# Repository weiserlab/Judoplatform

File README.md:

A Platform for learning and prototyping low-power wireless embedded systems

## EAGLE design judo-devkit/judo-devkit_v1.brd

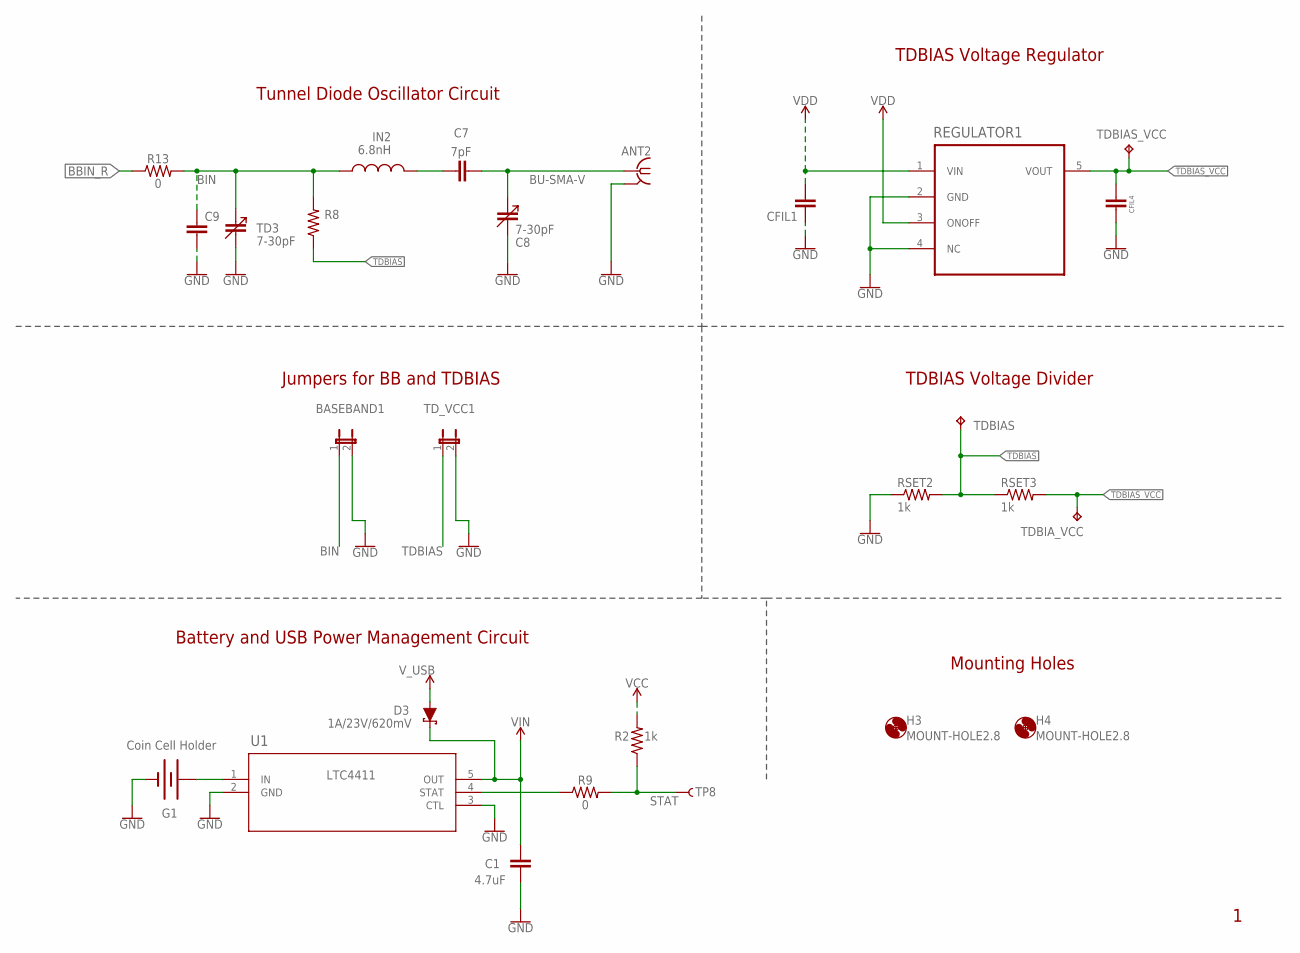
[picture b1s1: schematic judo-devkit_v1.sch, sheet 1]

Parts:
BASEBAND1: JP1E; JP1
C1: 4.7uF; C0603
C7: 7pF; C0603
C8: 7-30pF; CTZ3
C9: CAP-0603; 0603
CFIL1, CFIL4: 0805_1; 0805_1PRIMARY
D3: 1A/23V/620mV; SOD-323
G1: Coin Cell Holder; BATTCON_20MM_4LEGS
H3, H4: MOUNT-HOLE2.8; 2,8
IN2: 6.8nH; 0603_1PRIMARY
R2: 1k; 0603
R8: RESISTOR0805-RES; 0805
R9, R13: 0; 0603
REGULATOR1: S-1313B20; SOT23-5
RSET2, RSET3: 1k; R0603
TD3: 7-30pF; CTZ3
TDBIAS: TPPAD1-17; P1-17
TDBIAS_VCC: TPPAD1-17; P1-17
TDBIA_VCC: TPPAD1-17; P1-17
TD_VCC1: JP1E; JP1
TP8: TEST-POINT3X5; PAD.03X.05
TUNNELDIODE2: BU-SMA-V
U1: LTC4411ES5TRMPBF; SOT-5_S_LIT; MANUFACTURER_PART_NUMBER LTC4411

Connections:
ANT2: C7.2, C8.+ (3), TUNNELDIODE2.1
BBIN_R: R13.1; also elsewhere on the board
BIN: BASEBAND1.1, C9.1, IN2.1, R8.2, R13.2, TD3.+ (3)
GND: BASEBAND1.2, C1.1, C8.- (4), C9.2, CFIL1.1, CFIL4.2, G1.NEGATIVE (-), REGULATOR1.2 (GND), REGULATOR1.4 (NC), RSET2.1, TD3.- (4), TD_VCC1.2, TUNNELDIODE2.2, TUNNELDIODE2.3 (2), TUNNELDIODE2.4 (2), TUNNELDIODE2.5 (2), U1.2 (GND), U1.3 (CTL); also elsewhere on the board
unnamed: G1.POSITIVE@1 (+), G1.POSITIVE@2 (+), G1.POSITIVE@3 (+), G1.POSITIVE@4 (+), U1.1 (IN)
unnamed: R9.1, U1.4 (STAT)
unnamed: C7.1, IN2.2
STAT: R2.1, R9.2, TP8.1
TDBIAS: R8.1, RSET2.2, RSET3.1, TDBIAS.TP, TD_VCC1.1
TDBIAS_VCC: CFIL4.1, REGULATOR1.5 (VOUT), RSET3.2, TDBIAS_VCC.TP, TDBIA_VCC.TP
VCC: R2.2; also elsewhere on the board
VDD: CFIL1.2, REGULATOR1.1 (VIN), REGULATOR1.3 (ONOFF); also elsewhere on the board
VIN: C1.2, D3.C, U1.5 (OUT); also elsewhere on the board
V_USB: D3.A; also elsewhere on the board

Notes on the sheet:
Battery and USB Power Management Circuit
Tunnel Diode Oscillator Circuit
Jumpers for BB and TDBIAS
TDBIAS Voltage Divider
TDBIAS Voltage Regulator
Mounting Holes

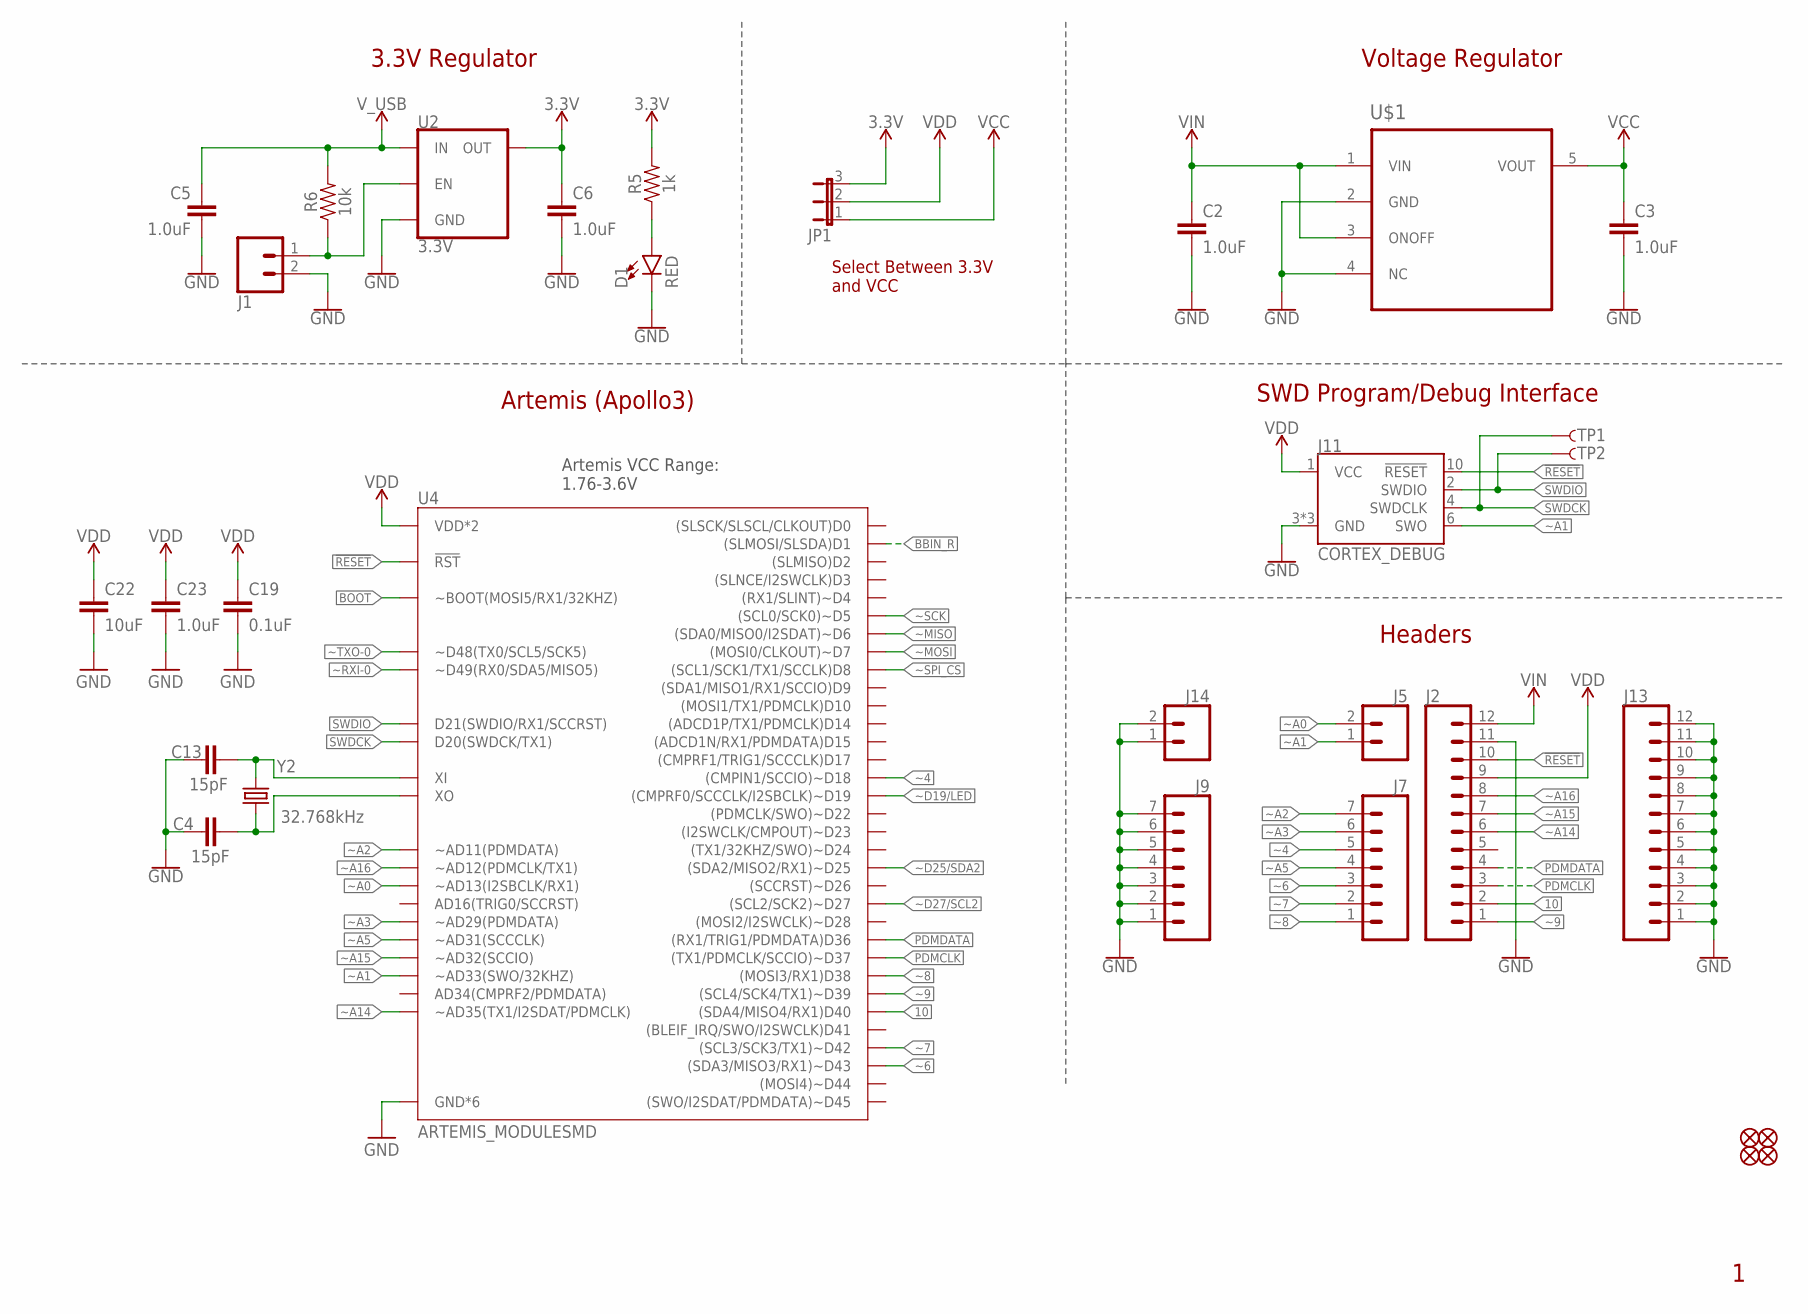
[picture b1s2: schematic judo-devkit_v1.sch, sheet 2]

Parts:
C2, C3, C5, C6, C23: 1.0uF; 0402-TIGHT
C4, C13: 15pF; 0603
C19: 0.1uF; 0402-TIGHT
C22: 10uF; 0603
D1: RED; LED-0603
FD1, FD2, FD3, FD4: FIDUCIALUFIDUCIAL; FIDUCIAL-MICRO
J1, J5, J14: CONN_021X02_NO_SILK; 1X02_NO_SILK
J2, J13: CONN_12NO_SILK; 1X12_NO_SILK
J7, J9: CONN_07NO_SILK; 1X07_NO_SILK
J11: CORTEX_DEBUG; 2X5-PTH-1.27MM-NO_SILK
JP1: JP2E; JP2
R5: 1k; 0603
R6: 10k; 0603
TP1, TP2: TEST-POINT3X5; PAD.03X.05
U2: 3.3V; SOT23-5
U4: ARTEMIS_MODULESMD; ARTEMIS_FP
U$1: CUSTOMCOMPONENTS_S-1313B20; CUSTOMCOMPONENTS_SOT23-5
Y2: 32.768kHz; CRYSTAL-SMD-3.2X1.5MM

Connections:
3.3V: C6.1, JP1.3, R5.2, U2.5 (OUT); also elsewhere on the board
10: J2.2, U4.D40 ((SDA4/MISO4/RX1)D40)
!RESET: J2.10, J11.10 (!RESET), U4.~RST (!RST); also elsewhere on the board
BBIN_R: U4.D1 ((SLMOSI/SLSDA)D1); also elsewhere on the board
BOOT: U4.BOOT (~BOOT(MOSI5/RX1/32KHZ)); also elsewhere on the board
GND: C2.2, C3.2, C4.1, C5.2, C6.2, C13.1, C19.1, C22.2, C23.2, D1.C, J1.2, J2.11, J9.1, J9.2, J9.3, J9.4, J9.5, J9.6, J9.7, J11.3 (GND), J11.5 (GND), J11.9 (GND), J13.1, J13.2, J13.3, J13.4, J13.5, J13.6, J13.7, J13.8, J13.9, J13.10, J13.11, J13.12, J14.1, J14.2, U2.2 (GND), U4.GND@1 (GND*6), U4.GND@22 (GND*6), U4.GND@38 (GND*6), U4.GND@39 (GND*6), U4.GND@47 (GND*6), U4.GND@59 (GND*6), U$1.2 (GND), U$1.4 (NC); also elsewhere on the board
unnamed: D1.A, R5.1
unnamed: C4.2, U4.XO, Y2.P$2 (2)
unnamed: C13.2, U4.XI, Y2.P$1 (1)
PDMCLK: J2.3, U4.~D37 ((TX1/PDMCLK/SCCIO)~D37)
PDMDATA: J2.4, U4.D36 ((RX1/TRIG1/PDMDATA)D36)
SWDCK: J11.4 (SWDCLK), TP1.1, U4.SWDCK (D20(SWDCK/TX1))
SWDIO: J11.2 (SWDIO), TP2.1, U4.SWDIO (D21(SWDIO/RX1/SCCRST))
VCC: C3.1, JP1.1, U$1.5 (VOUT); also elsewhere on the board
VDD: C19.2, C22.1, C23.1, J2.9, J11.1 (VCC), JP1.2, U4.VDD@36 (VDD*2), U4.VDD@37 (VDD*2); also elsewhere on the board
VIN: C2.1, J2.12, U$1.1 (VIN), U$1.3 (ONOFF); also elsewhere on the board
VREG_EN1: J1.1, R6.1, U2.3 (EN)
V_USB: C5.1, R6.2, U2.1 (IN); also elsewhere on the board
~4: J7.5, U4.~D18 ((CMPIN1/SCCIO)~D18)
~6: J7.3, U4.~D43 ((SDA3/MISO3/RX1)~D43)
~7: J7.2, U4.~D42 ((SCL3/SCK3/TX1)~D42)
~8: J7.1, U4.D38 ((MOSI3/RX1)D38)
~9: J2.1, U4.~D39 ((SCL4/SCK4/TX1)~D39)
~A0: J5.2, U4.~AD13 (~AD13(I2SBCLK/RX1))
~A1: J5.1, J11.6 (SWO), U4.~AD33/SWO (~AD33(SWO/32KHZ))
~A2: J7.7, U4.~AD11 (~AD11(PDMDATA))
~A3: J7.6, U4.~AD29 (~AD29(PDMDATA))
~A5: J7.4, U4.~AD31 (~AD31(SCCCLK))
~A14: J2.6, U4.~AD35 (~AD35(TX1/I2SDAT/PDMCLK))
~A15: J2.7, U4.~AD32 (~AD32(SCCIO))
~A16: J2.8, U4.~AD12 (~AD12(PDMCLK/TX1))
~D19/LED: U4.~D19 ((CMPRF0/SCCCLK/I2SBCLK)~D19); also elsewhere on the board
~D25/SDA2: U4.~D25 ((SDA2/MISO2/RX1)~D25); also elsewhere on the board
~D27/SCL2: U4.~D27 ((SCL2/SCK2)~D27); also elsewhere on the board
~MISO: U4.~D6 ((SDA0/MISO0/I2SDAT)~D6); also elsewhere on the board
~MOSI: U4.D7 ((MOSI0/CLKOUT)~D7); also elsewhere on the board
~RXI-0: U4.RXI-0 (~D49(RX0/SDA5/MISO5)); also elsewhere on the board
~SCK: U4.~D5 ((SCL0/SCK0)~D5); also elsewhere on the board
~SPI_CS: U4.D8 ((SCL1/SCK1/TX1/SCCLK)D8); also elsewhere on the board
~TXO-0: U4.TXO-0 (~D48(TX0/SCL5/SCK5)); also elsewhere on the board

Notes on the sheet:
SWD Program/Debug Interface
Headers
Artemis (Apollo3)
Voltage Regulator
Artemis VCC Range: 1.76-3.6V
3.3V Regulator
Select Between 3.3V and VCC

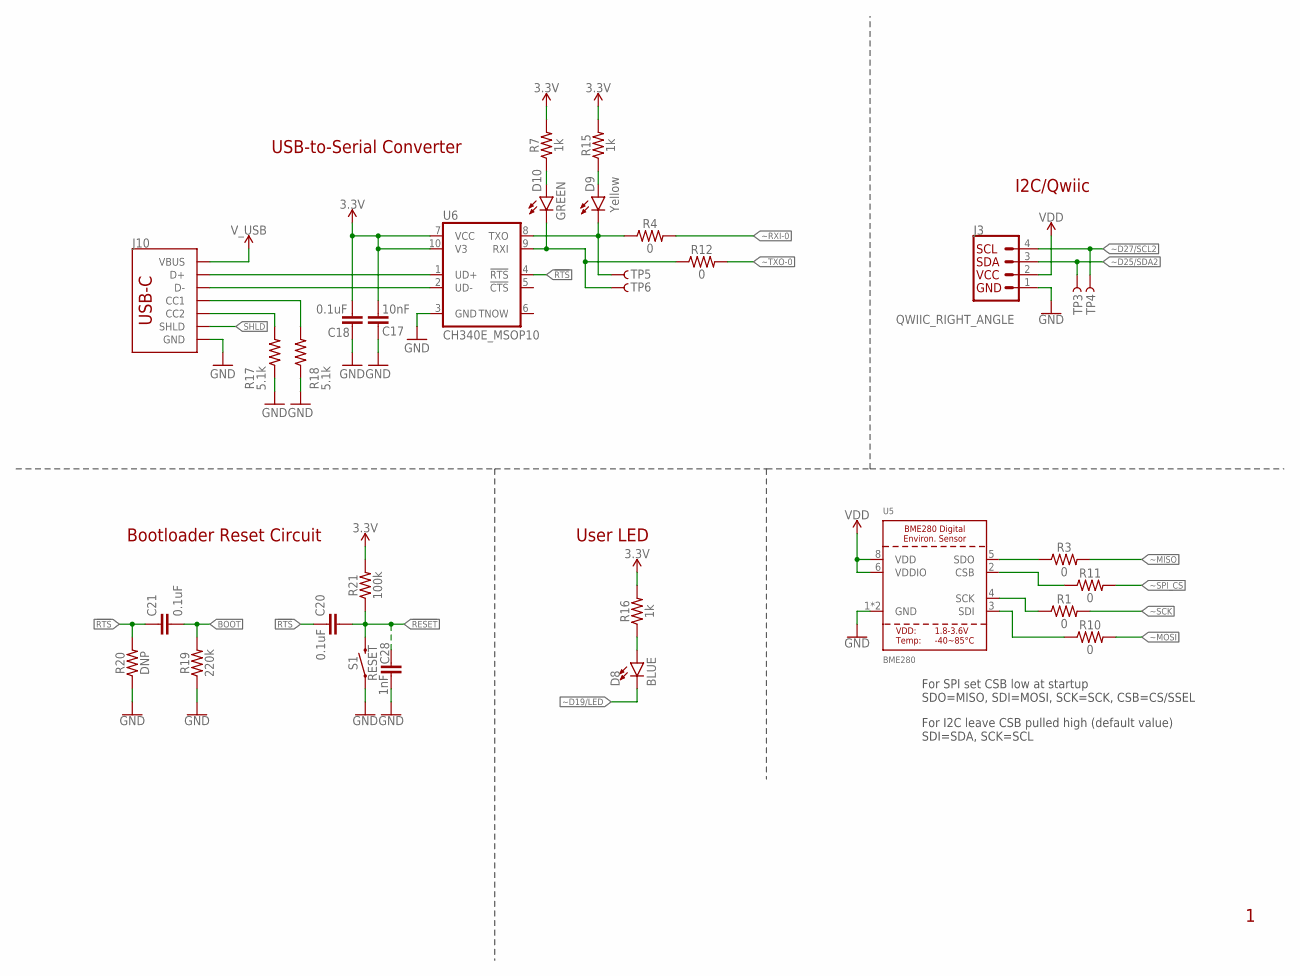
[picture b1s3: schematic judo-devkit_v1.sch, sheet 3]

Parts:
C17: 10nF; 0603
C18, C20, C21: 0.1uF; 0603
C28: 1nF; 0603
D8: BLUE; LED-0603
D9: Yellow; LED-0603
D10: GREEN; LED-0603
J3: QWIIC_RIGHT_ANGLE; JST04_1MM_RA
J10: USB Female Type C Connector; USB-C-16P-2LAYER-PADS
R1, R3, R4, R10, R11, R12: 0; 0603
R7, R15, R16: 1k; 0603
R17, R18: 5.1k; 0603
R19: 220k; 0603
R20: DNP; 0603
R21: 100k; 0603
S1: RESET; TACTILE_SWITCH_SMD_4.6X2.8MM
TP3, TP4, TP5, TP6: TEST-POINT3X5; PAD.03X.05
U5: BME280
U6: CH340E_MSOP10; MSOP10

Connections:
3.3V: C17.1, C18.1, R7.2, R15.2, R16.2, R21.2, U6.7 (VCC), U6.10 (V3); also elsewhere on the board
!RESET: C20.2, C28.1, R21.1, S1.3 (2), S1.4 (2); also elsewhere on the board
!RTS: C20.1, C21.1, R20.2, U6.4 (!RTS)
BOOT: C21.2, R19.2; also elsewhere on the board
CC1: J10.A5 (CC1), R18.2
CC2: J10.B5 (CC2), R17.2
D+1: J10.A6 (D+), J10.B6 (D+), U6.1 (UD+)
D-1: J10.A7 (D-), J10.B7 (D-), U6.2 (UD-)
GND: C17.2, C18.2, C28.2, J3.1, J10.GND, J10.GND2 (GND), R17.1, R18.1, R19.1, R20.1, S1.1, S1.2 (1), U5.1 (GND), U5.7 (GND), U6.3 (GND); also elsewhere on the board
unnamed: R11.1, U5.2 (CSB)
unnamed: R3.1, U5.5 (SDO)
unnamed: D8.A, R16.1
unnamed: D10.A, R7.1
unnamed: D9.A, R15.1
unnamed: R1.1, U5.4 (SCK)
unnamed: R10.1, U5.3 (SDI)
RXI-0_R: D9.C, R4.1, TP5.1, U6.8 (TXO)
SHLD: J10.SHLD1 (SHLD), J10.SHLD2 (SHLD), J10.SHLD3 (SHLD), J10.SHLD4 (SHLD)
TXO-0_R: D10.C, R12.1, TP6.1, U6.9 (RXI)
VDD: J3.2, U5.6 (VDDIO), U5.8 (VDD); also elsewhere on the board
V_USB: J10.VBUS1 (VBUS), J10.VBUS2 (VBUS); also elsewhere on the board
~D19/LED: D8.C; also elsewhere on the board
~D25/SDA2: J3.3, TP3.1; also elsewhere on the board
~D27/SCL2: J3.4, TP4.1; also elsewhere on the board
~MISO: R3.2; also elsewhere on the board
~MOSI: R10.2; also elsewhere on the board
~RXI-0: R4.2; also elsewhere on the board
~SCK: R1.2; also elsewhere on the board
~SPI_CS: R11.2; also elsewhere on the board
~TXO-0: R12.2; also elsewhere on the board

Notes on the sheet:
USB-to-Serial Converter
Bootloader Reset Circuit
User LED
I2C/Qwiic
For SPI set CSB low at startup SDO=MISO, SDI=MOSI, SCK=SCK, CSB=CS/SSEL
For I2C leave CSB pulled high (default value) SDI=SDA, SCK=SCL

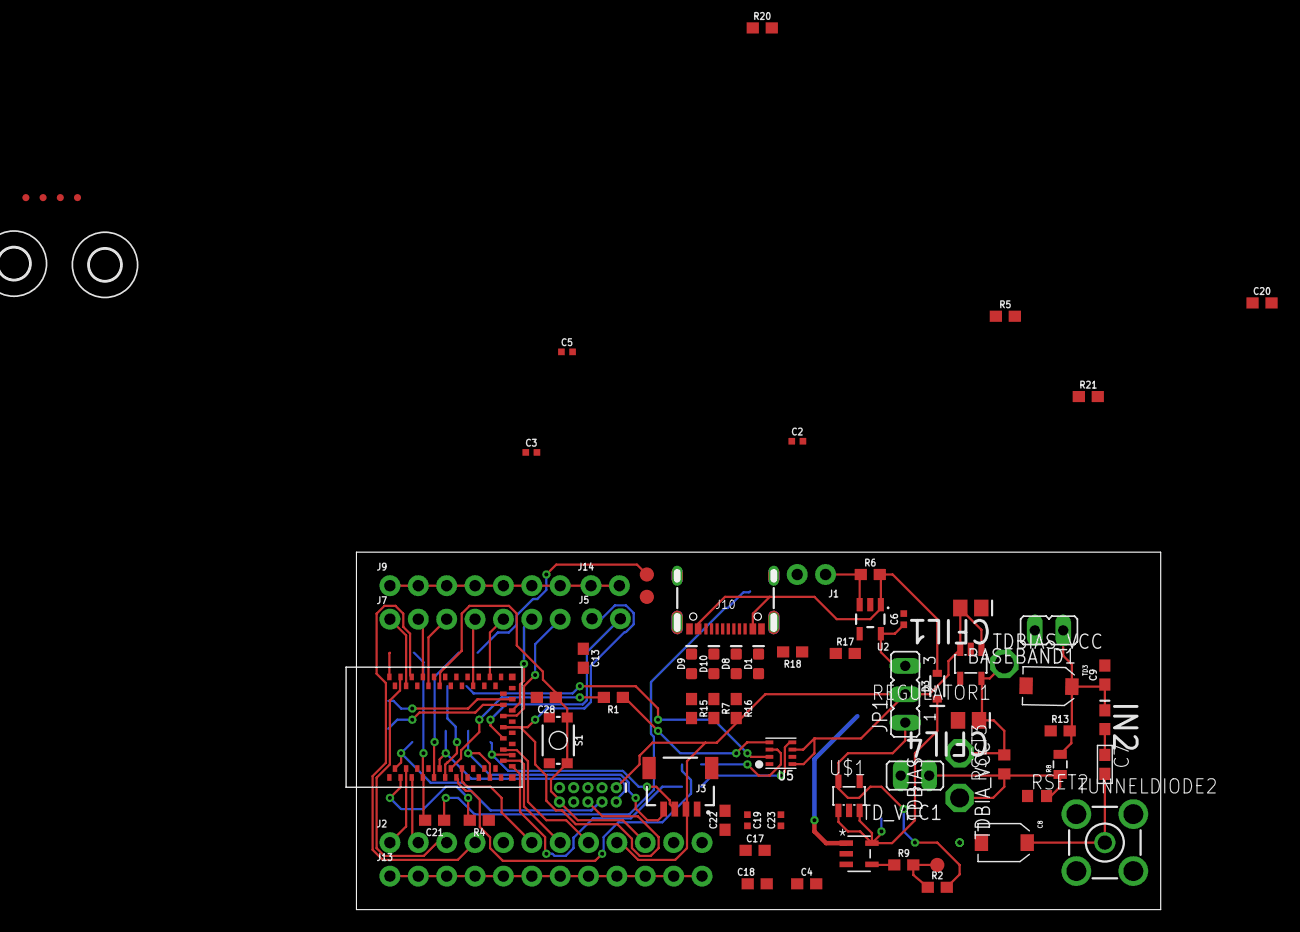
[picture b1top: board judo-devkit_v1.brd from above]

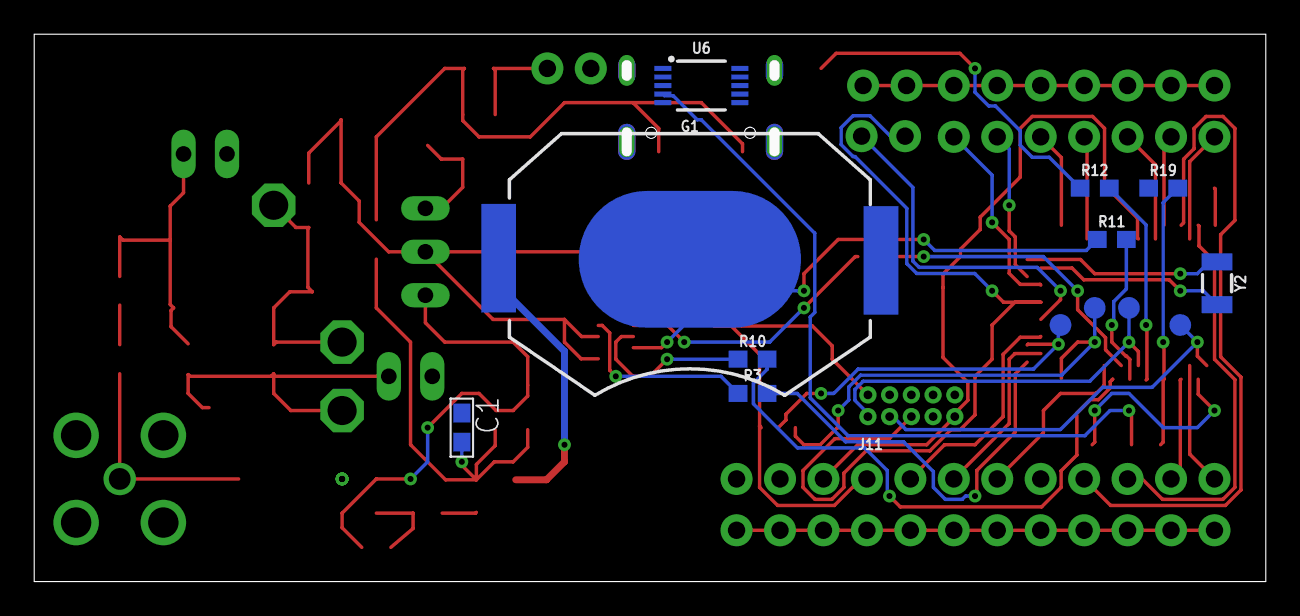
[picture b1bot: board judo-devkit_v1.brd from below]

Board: 2 copper layers, 71.4 x 31.4 mm, 89 parts (13 on the bottom side), 63 nets.

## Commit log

2023-12-05 new schematic and reorganized things
2023-12-08 added apollo3, power management
2023-12-11 updated apollo and power management
2023-12-12 added sensors and cleaned up schematic
2023-12-15 changed regulator
2024-01-11 added board
2024-01-30 routing
2024-02-03 more routing, it looks pretty messy sadly

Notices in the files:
parts and their libraries:
SparkFun-Capacitors: Licensing: CC v3.0 Share-Alike You are welcome to use this library for commercial purposes.
SparkFun-Capacitors: Licensing: Creative Commons ShareAlike 4.0 International - https://creativecommons.org/licenses/by-sa/4.0
